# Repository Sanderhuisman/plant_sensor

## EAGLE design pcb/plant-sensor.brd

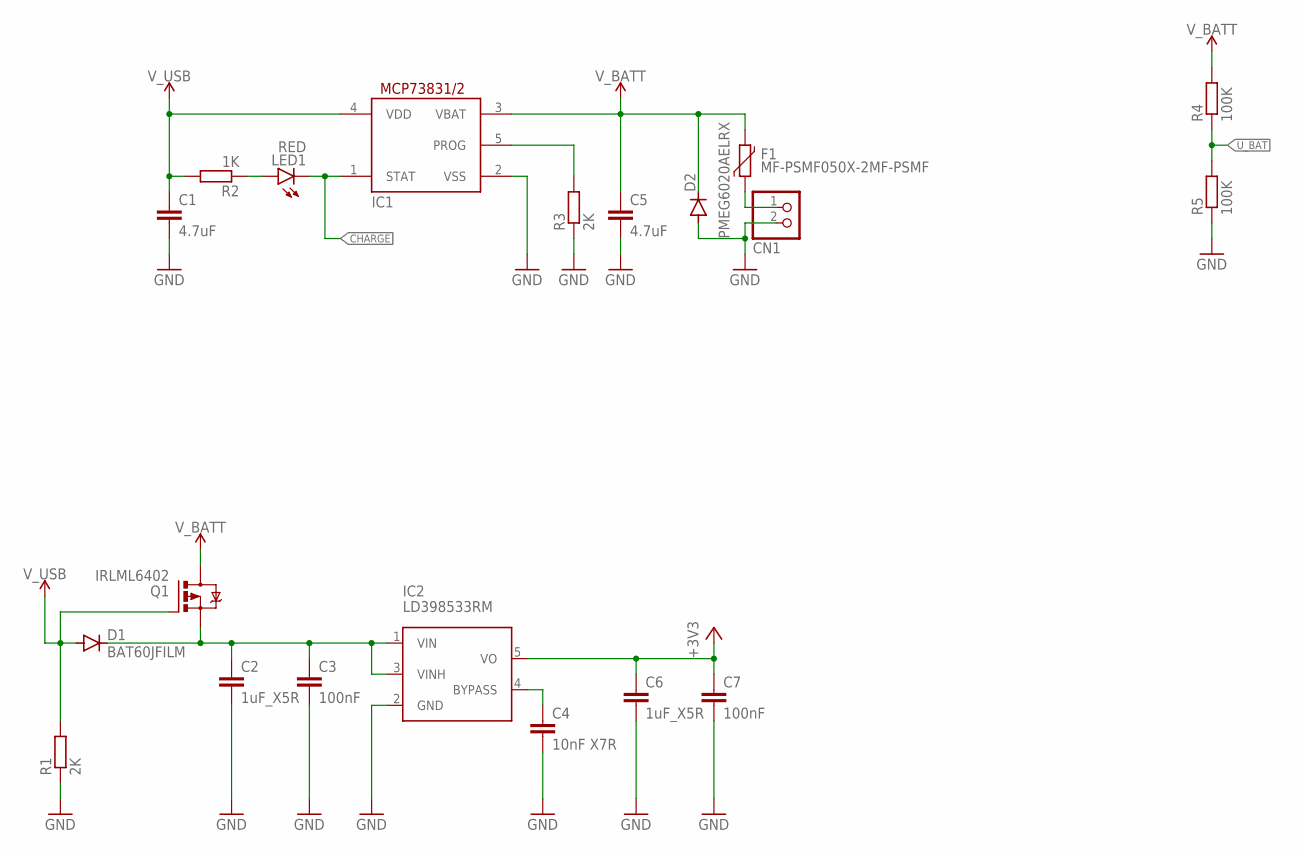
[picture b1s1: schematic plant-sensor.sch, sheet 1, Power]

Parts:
C1, C5: 4.7uF; C0805
C2, C6: 1uF_X5R; C0805
C3, C7: 100nF; C0805
C4: 10nF X7R; C0805
CN1: JST_2PIN-SMT-RA; JST-PH-2-SMT-RA
D1: BAT60JFILM; SOD323-W
D2: PMEG6020AELRX; SOD123
F1: MF-PSMF050X-2MF-PSMF; R0805
IC1: MCP73831/OT; SOT23-5L
IC2: LD398533RM; SOT23-5L
LED1: RED; CHIP-LED0805
Q1: IRLML6402; MICRO3
R1, R3: 2K; R0805
R2: 1K; R0805
R4, R5: 100K; R0805

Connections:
+3V3: C6.1, C7.1, IC2.5 (VO); also elsewhere on the board
CHARGE: IC1.1 (STAT), LED1.C; also elsewhere on the board
GND: C1.2, C2.2, C3.2, C4.2, C5.2, C6.2, C7.2, CN1.2 (1), D2.A, IC1.2 (VSS), IC2.2 (GND), R1.1, R3.1, R5.1; also elsewhere on the board
unnamed: CN1.1 (2), F1.1
unnamed: C2.1, C3.1, D1.C, IC2.1 (VIN), IC2.3 (VINH), Q1.2 (S)
unnamed: LED1.A, R2.1
unnamed: IC1.5 (PROG), R3.2
unnamed: C4.1, IC2.4 (BYPASS)
U_BAT: R4.1, R5.2; also elsewhere on the board
V_BATT: C5.1, D2.C, F1.2, IC1.3 (VBAT), Q1.3 (D), R4.2
V_USB: C1.1, D1.A, IC1.4 (VDD), Q1.1 (G), R1.2, R2.2; also elsewhere on the board

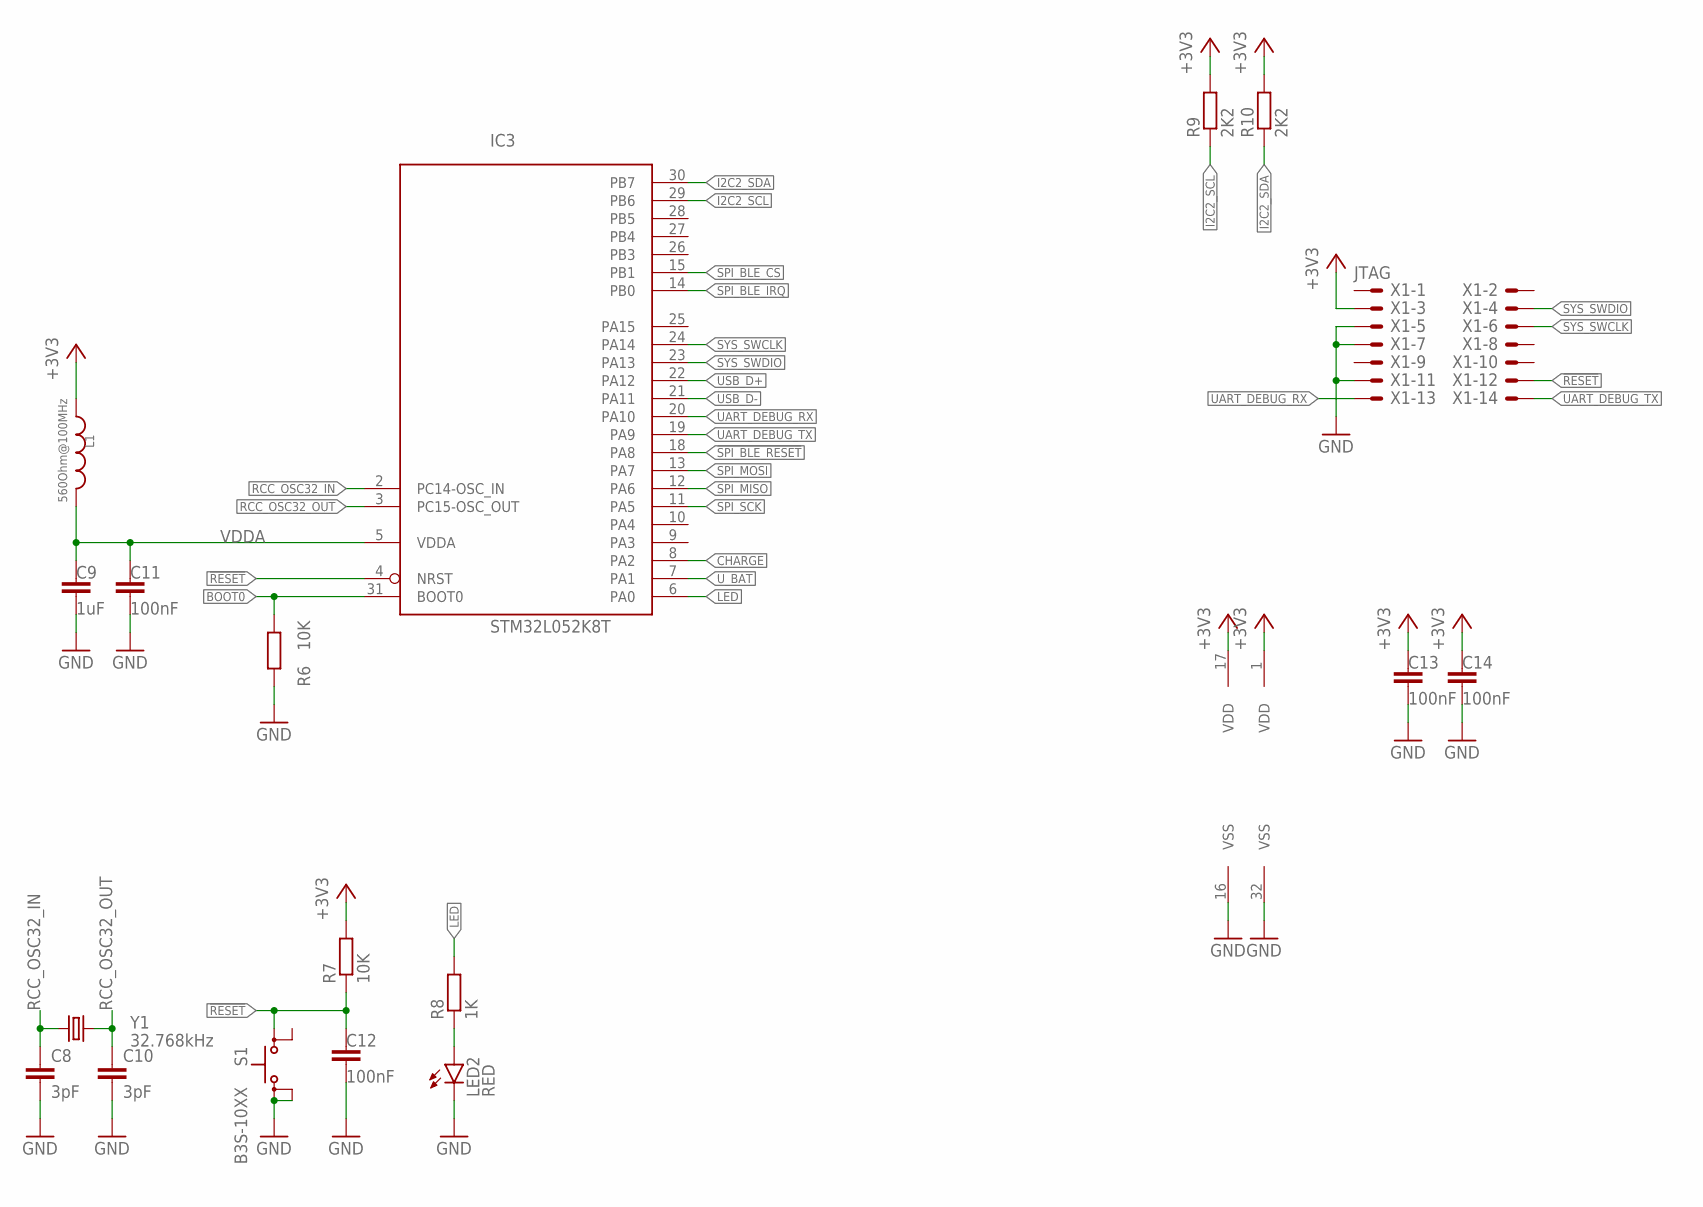
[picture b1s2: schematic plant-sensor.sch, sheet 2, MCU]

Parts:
C8, C10: 3pF; C0805
C9: 1uF; C0805
C11, C12, C13, C14: 100nF; C0805
IC3: STM32L052K8T; LQFP32
L1: 560Ohm@100MHz; WE-CBA_0805(W=4)
LED2: RED; CHIP-LED0805
R6, R7: 10K; R0805
R8: 1K; R0805
R9, R10: 2K2; R0805
S1: B3S-10XX
X1: JTAG; 1365-14
Y1: 32.768kHz; XTAL_ABS25-32.768KHZ-6-1-T

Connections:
!RESET: C12.2, IC3.4 (NRST), R7.1, S1.1, X1.12
!SPI_BLE_RESET: IC3.18 (PA8); also elsewhere on the board
+3V3: C13.2, C14.2, IC3.17 (VDD), L1.1, R7.2, R9.2, R10.2, X1.3; also elsewhere on the board
BOOT0: IC3.31 (BOOT0), R6.2
CHARGE: IC3.8 (PA2); also elsewhere on the board
GND: C8.2, C9.1, C10.2, C11.1, C12.1, C13.1, C14.1, IC3.16 (VSS), IC3.32 (VSS), LED2.C, R6.1, S1.3 (S), S1.4 (S1), X1.5, X1.7, X1.11; also elsewhere on the board
I2C2_SCL: IC3.29 (PB6), R9.1; also elsewhere on the board
I2C2_SDA: IC3.30 (PB7), R10.1; also elsewhere on the board
LED: IC3.6 (PA0), R8.2
unnamed: LED2.A, R8.1
RCC_OSC32_IN: C8.1, IC3.2 (PC14-OSC_IN), Y1.1
RCC_OSC32_OUT: C10.1, IC3.3 (PC15-OSC_OUT), Y1.4 (2)
SPI_BLE_CS: IC3.15 (PB1); also elsewhere on the board
SPI_BLE_IRQ: IC3.14 (PB0); also elsewhere on the board
SPI_MISO: IC3.12 (PA6); also elsewhere on the board
SPI_MOSI: IC3.13 (PA7); also elsewhere on the board
SPI_SCK: IC3.11 (PA5); also elsewhere on the board
SYS_SWCLK: IC3.24 (PA14), X1.6
SYS_SWDIO: IC3.23 (PA13), X1.4
UART_DEBUG_RX: IC3.20 (PA10), X1.13
UART_DEBUG_TX: IC3.19 (PA9), X1.14
USB_D+: IC3.22 (PA12); also elsewhere on the board
USB_D-: IC3.21 (PA11); also elsewhere on the board
U_BAT: IC3.7 (PA1); also elsewhere on the board
VDDA: C9.2, C11.2, IC3.5 (VDDA), L1.2

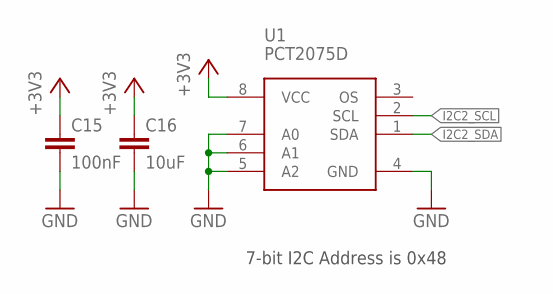
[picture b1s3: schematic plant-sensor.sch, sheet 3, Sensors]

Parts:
C15: 100nF; C0805
C16: 10uF; C0805
U1: PCT2075D; SOIC8_150MIL

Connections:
+3V3: C15.1, C16.1, U1.8 (VCC); also elsewhere on the board
GND: C15.2, C16.2, U1.4 (GND), U1.5 (A2), U1.6 (A1), U1.7 (A0); also elsewhere on the board
I2C2_SCL: U1.2 (SCL); also elsewhere on the board
I2C2_SDA: U1.1 (SDA); also elsewhere on the board

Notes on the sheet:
7-bit I2C Address is 0x48

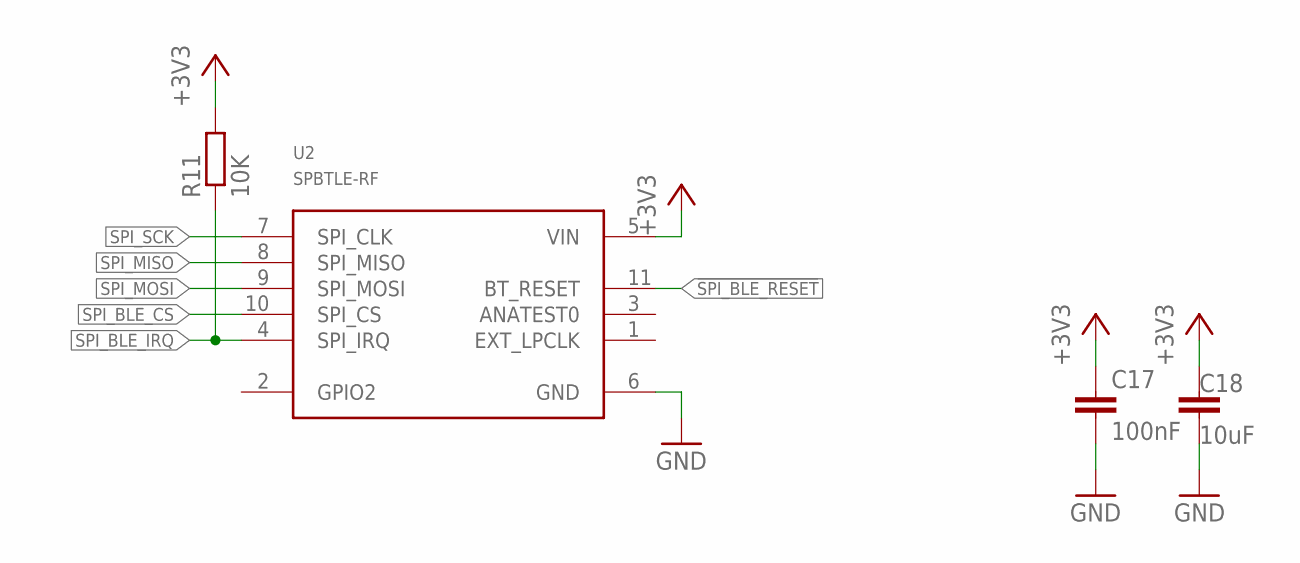
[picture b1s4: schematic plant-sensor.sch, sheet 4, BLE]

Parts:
C17: 100nF; C0805
C18: 10uF; C0805
R11: 10K; R0805
U2: SPBTLE-RF; XCVR_SPBTLE-RF

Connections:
!SPI_BLE_RESET: U2.11 (BT_RESET); also elsewhere on the board
+3V3: C17.1, C18.2, R11.2, U2.5 (VIN); also elsewhere on the board
GND: C17.2, C18.1, U2.6 (GND); also elsewhere on the board
SPI_BLE_CS: U2.10 (SPI_CS); also elsewhere on the board
SPI_BLE_IRQ: R11.1, U2.4 (SPI_IRQ); also elsewhere on the board
SPI_MISO: U2.8 (SPI_MISO); also elsewhere on the board
SPI_MOSI: U2.9 (SPI_MOSI); also elsewhere on the board
SPI_SCK: U2.7 (SPI_CLK); also elsewhere on the board

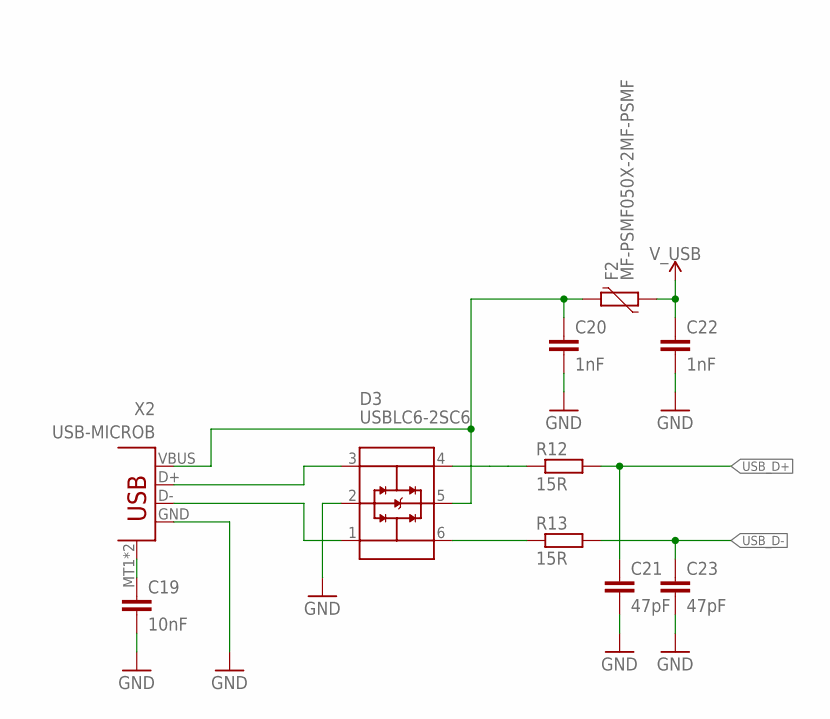
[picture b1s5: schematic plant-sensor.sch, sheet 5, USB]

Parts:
C19: 10nF; C0805
C20, C22: 1nF; C0805
C21, C23: 47pF; C0805
D3: USBLC6-2SC6; SOT95P280X145-6N
F2: MF-PSMF050X-2MF-PSMF; R0805
R12, R13: 15R; R0805
X2: USB-MICROB

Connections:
GND: C19.2, C20.2, C21.2, C22.2, C23.2, D3.2 (GND), X2.GND; also elsewhere on the board
unnamed: C20.1, D3.5 (VBUS), F2.2, X2.VBUS
unnamed: D3.3 (I/O2_1), X2.D+
unnamed: C19.1, X2.MT1 (MT), X2.MT2 (MT)
unnamed: D3.6 (I/O1_2), R13.1
unnamed: D3.1 (I/O1_1), X2.D-
unnamed: D3.4 (I/O2_2), R12.1
USB_D+: C21.1, R12.2; also elsewhere on the board
USB_D-: C23.1, R13.2; also elsewhere on the board
V_USB: C22.1, F2.1; also elsewhere on the board

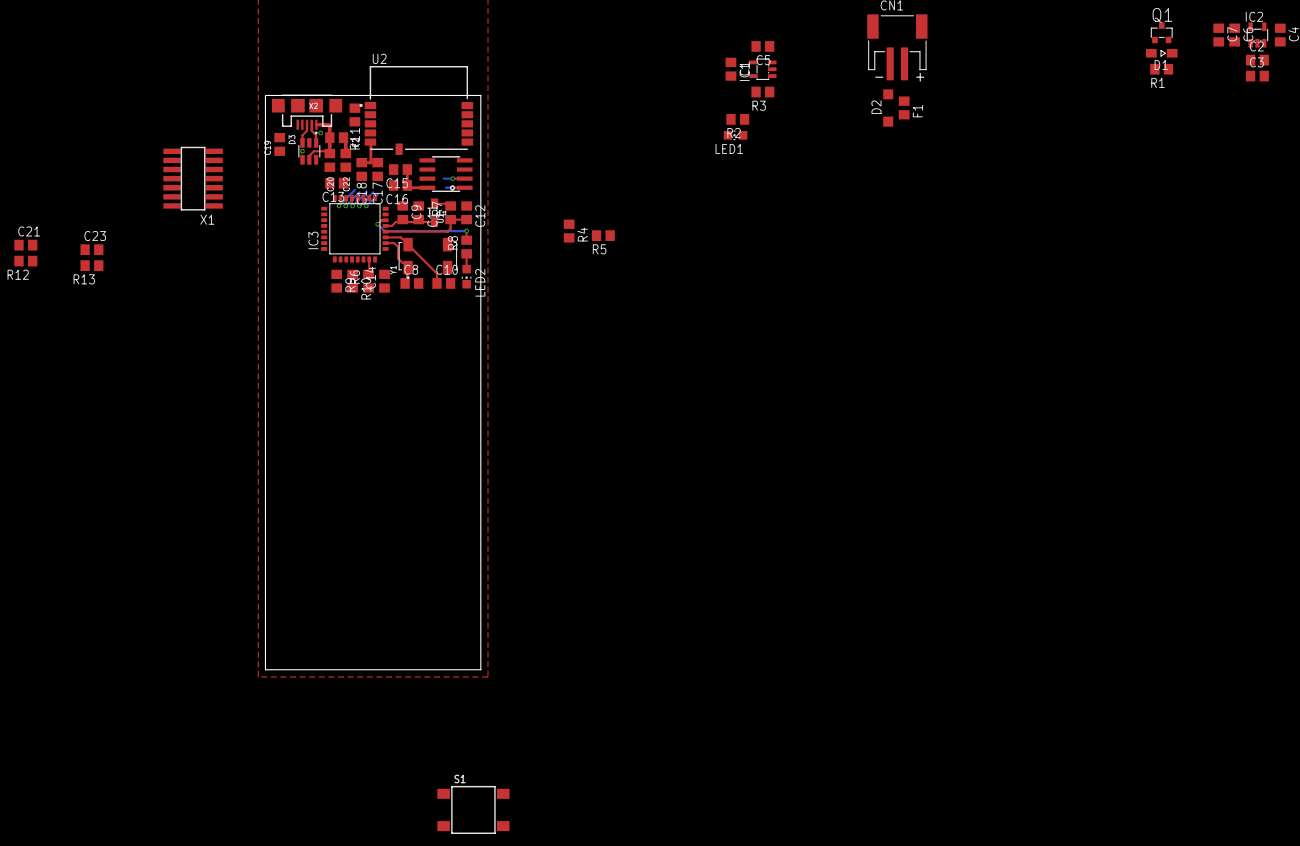
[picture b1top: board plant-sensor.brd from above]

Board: 2 copper layers, 30.0 x 80.0 mm, 55 parts (0 on the bottom side), 38 nets.

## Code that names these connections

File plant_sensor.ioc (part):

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Mcu.Name=STM32L052K(6-8)Tx
Mcu.Package=LQFP32
Mcu.UserName=STM32L052K8Tx
PA0.Mode=IN0
PA0.Signal=ADC_IN0
PA1.GPIOParameters=GPIO_Label
PA1.GPIO_Label=CHARGE
PA1.Signal=GPIO_Input
PA10.Mode=Asynchronous
PA10.Signal=USART1_RX
PA11.Mode=Device
PA11.Signal=USB_DM
PA12.Mode=Device
PA12.Signal=USB_DP
PA13.Mode=Serial_Wire
PA13.Signal=SYS_SWDIO
PA14.Mode=Serial_Wire
PA14.Signal=SYS_SWCLK
PA4.GPIOParameters=GPIO_Label
PA4.GPIO_Label=LED
PA4.Signal=GPIO_Output
PA5.Mode=Full_Duplex_Master
PA5.Signal=SPI1_SCK
PA6.Mode=Full_Duplex_Master
PA6.Signal=SPI1_MISO
PA7.Mode=Full_Duplex_Master
PA7.Signal=SPI1_MOSI
PA8.GPIOParameters=GPIO_Label
PA8.GPIO_Label=SPI_BLE_RESET
PA8.Signal=GPIO_Output
PA9.Mode=Asynchronous
PA9.Signal=USART1_TX
PB0.GPIOParameters=GPIO_Label
PB0.GPIO_Label=SPI_BLE_IRQ
PB0.Signal=GPXTI0
PB1.GPIOParameters=GPIO_Label
PB1.GPIO_Label=SPI_BLE_CS
PB1.Signal=GPIO_Output
PB3.Mode=G5_IO1-Sampling
PB3.Signal=TSC_G5_IO1
PB4.Mode=G5_IO2-Channel
PB4.Signal=TSC_G5_IO2
PB6.Mode=I2C
PB6.Signal=I2C1_SCL
PB7.Mode=I2C
PB7.Signal=I2C1_SDA
PC14-OSC32_IN.Mode=LSE-External-Oscillator
PC14-OSC32_IN.Signal=RCC_OSC32_IN
PC15-OSC32_OUT.Mode=LSE-External-Oscillator
PC15-OSC32_OUT.Signal=RCC_OSC32_OUT
RCC.SYSCLKFreq_VALUE=32000000
RCC.SYSCLKSource=RCC_SYSCLKSOURCE_PLLCLK
board=custom

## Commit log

2019-03-02 Added i2c moisture sensor repo
2019-03-02 Added stemma
2019-11-03 eagle
2019-11-04 layouting
2019-11-04 Added chirp project

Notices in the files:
parts and their libraries:
Wurth_Automotive_WE-CBA: Copyright: Würth Elektronik
SparkFun-PowerSymbols: Licensing: Creative Commons ShareAlike 4.0 International - https://creativecommons.org/licenses/by-sa/4.0
